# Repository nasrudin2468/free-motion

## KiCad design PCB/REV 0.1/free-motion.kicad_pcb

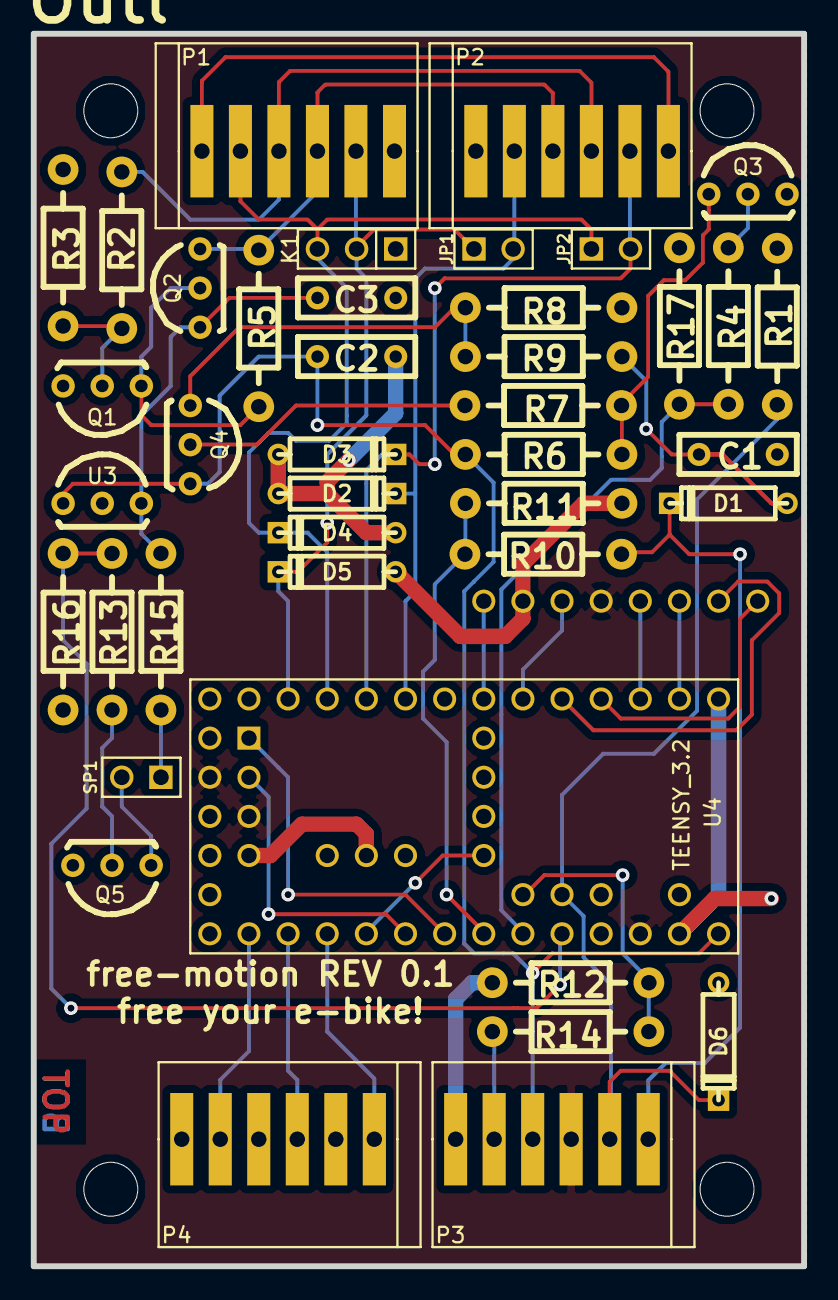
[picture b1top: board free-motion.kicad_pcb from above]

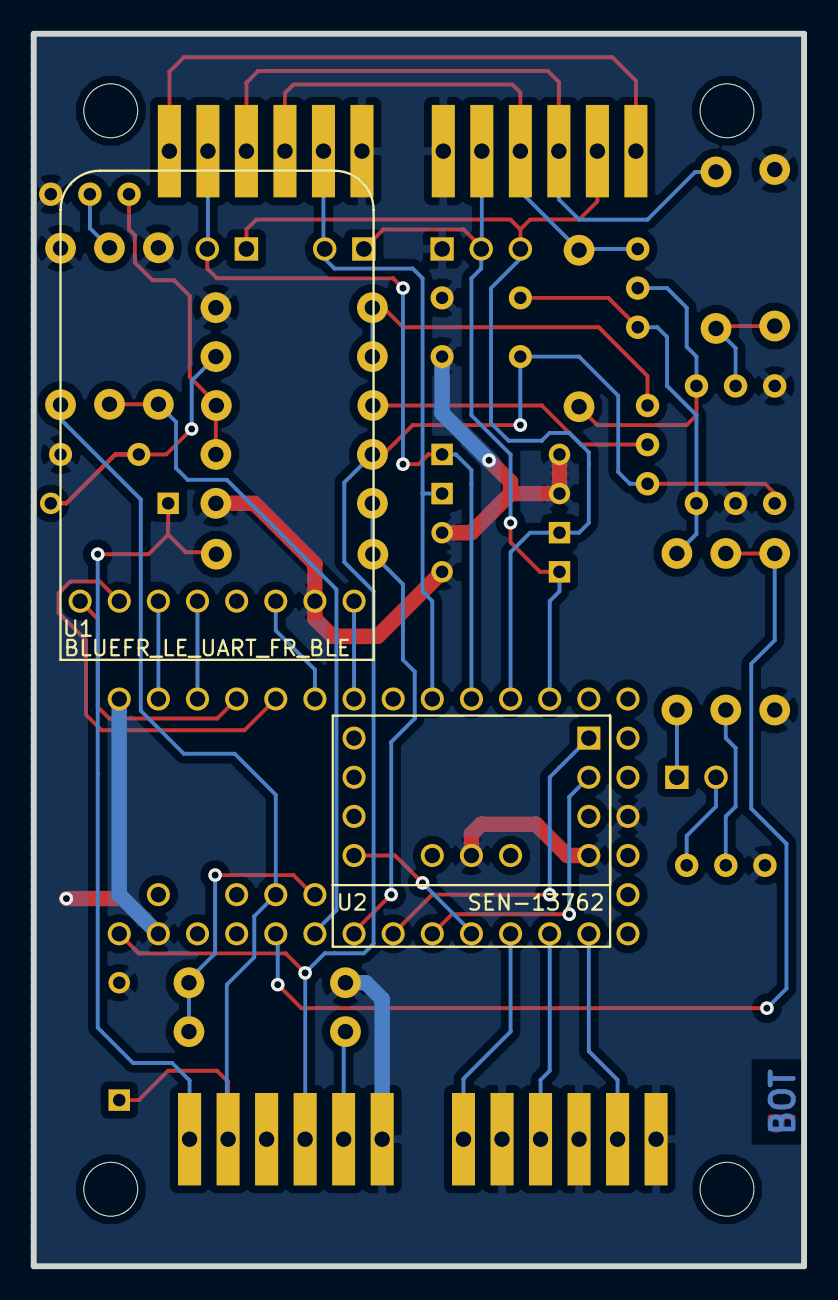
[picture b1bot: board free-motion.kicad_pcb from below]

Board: 2 copper layers, 50.0 x 80.0 mm, 44 parts (2 on the bottom side), 40 nets.

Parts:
C1, C2, C3: 1uF; Capacitor7x2.5RM5
D1: DIODE; D3
D2, D3, D4, D5, D6: ZENER 5V; D3
JP1, JP2: JUMPER; PIN_ARRAY_2X1
K1: CONN_3; PIN_ARRAY_3X1
Outl: EuroBoard_viertel_Type-I_80mmX50mm_holes
P1, P2, P3, P4: PHOENIX1989780; Phoenix_PTFSA_0.5
Q1, Q3, Q5: BC547; TO-92-Free-inline-wide
Q2: LP0701N3-G; TO-92-FET-inline-wide-SGD
Q4: BC557; TO-92-Free-inline-wide
R1: 6K8; Resistor_Horizontal_RM10mm_22Apr2011
R2, R4, R6, R7, R9, R13, R16: 1K; Resistor_Horizontal_RM10mm_22Apr2011
R3, R15: 100R; Resistor_Horizontal_RM10mm_22Apr2011
R5, R11, R12: 2K; Resistor_Horizontal_RM10mm_22Apr2011
R8: 470R; Resistor_Horizontal_RM10mm_22Apr2011
R10, R14: 3K9; Resistor_Horizontal_RM10mm_22Apr2011
R17: 1K1; Resistor_Horizontal_RM10mm_22Apr2011
SP1: CPE-165; PIN_ARRAY_2X1
U1: BLUEFR_LE_UART_FR_BLE; Bluefruit_LE_UART
U2: SEN-13762
U3: 78L05; TO-92-LM78L05
U4: TEENSY_3.2; TEENSY3.2

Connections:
+3.3V: P3.3, U1.5, U2.3, U4.26, U4.48
+5V: C2.1, P3.4, Q4.3, R6.1, U3.VO, U4.28
+12V: C3.1, Q2.S, R15.1, U3.VI
AIN_C: P3.5, R14.2
BLE_CTS: U1.2, U4.5
BLE_DFU: U1.8, U4.7
BLE_MOD: U1.1, U4.4
BLE_RTS: U1.6, U4.6
BLE_RXI: U1.4, U4.3
BLE_TXO: U1.3, U4.2
GND: C1.2, C2.2, C3.2, D2.1, D3.1, D4.1, D5.1, D6.1, K1.1, P1.6, P2.1, P3.6, P4.2, P4.4, P4.6, Q1.3, Q3.3, Q5.3, R1.1, R3.2, R8.2, R11.2, R12.2, R16.2, R17.2, U1.7, U2.4, U2.6, U3.GND, U4.1, U4.27, U4.49
IMU_INT: U2.8, U4.19
IMU_SCL: U2.1, U4.21
IMU_SDA: U2.2, U4.20
unnamed: P1.1, P2.6
unnamed: Q5.1, SP1.2
unnamed: Q1.2, R2.2, R3.1
unnamed: P1.3, P2.4, R2.1
unnamed: P1.4, P2.3, Q2.D, R5.1
unnamed: Q1.1, Q2.G, R5.2
unnamed: Q5.2, R13.2
unnamed: R12.1, R14.1, U4.43
unnamed: C1.1, D1.1, R9.2
unnamed: Q4.2, R7.2
unnamed: Q3.2, R4.2
unnamed: P4.5, U4.16
unnamed: Q4.1, R8.1, R9.1
unnamed: R15.2, SP1.1
unnamed: P4.1, U4.18
unnamed: P4.3, U4.17
unnamed: Q3.1, R6.2, R7.1
PHD_C: D6.2, P3.2, R1.2, U4.44
RXC: D5.2, JP1.1, K1.2, P1.5, U4.12
RXD: D3.2, JP2.2, P2.5, U4.10
SPKR: R13.1, R16.1, U4.24
TMM_C: D1.2, P3.1, R10.1
TMM_FB: R10.2, R11.1, U4.22
TMM_OUT: R4.1, R17.1, U4.23
TXC: D4.2, JP2.1, K1.3, P1.2, U4.11
TXD: D2.2, JP1.2, P2.2, U4.9

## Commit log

2017-08-03 Initial commit. contains main notes from protocol analysis, partlist for prototype and latest code of the python tool
2017-08-21 Create LICENSE
2017-08-21 folder restructured. - /software/pye-motion deleted - has now own repository: "pye-motion" - /documents deleted - Partslist moved
2017-08-22 Initial circuit / PCB design REV 0.1 - circuit diagram created - pcb created - partlists created - /Notes/protocol analysis: latest findings included
2017-08-23 - derived missing gerberfiles, deleted double partlists
2017-08-23 - removed unused label, rederived all gerberfiles
2017-08-27 extended protocol analysis with parameter set for 2013 Neo Cross EU (36V)
2017-10-07 Add readme file containing known PCB errors of REV0.1
